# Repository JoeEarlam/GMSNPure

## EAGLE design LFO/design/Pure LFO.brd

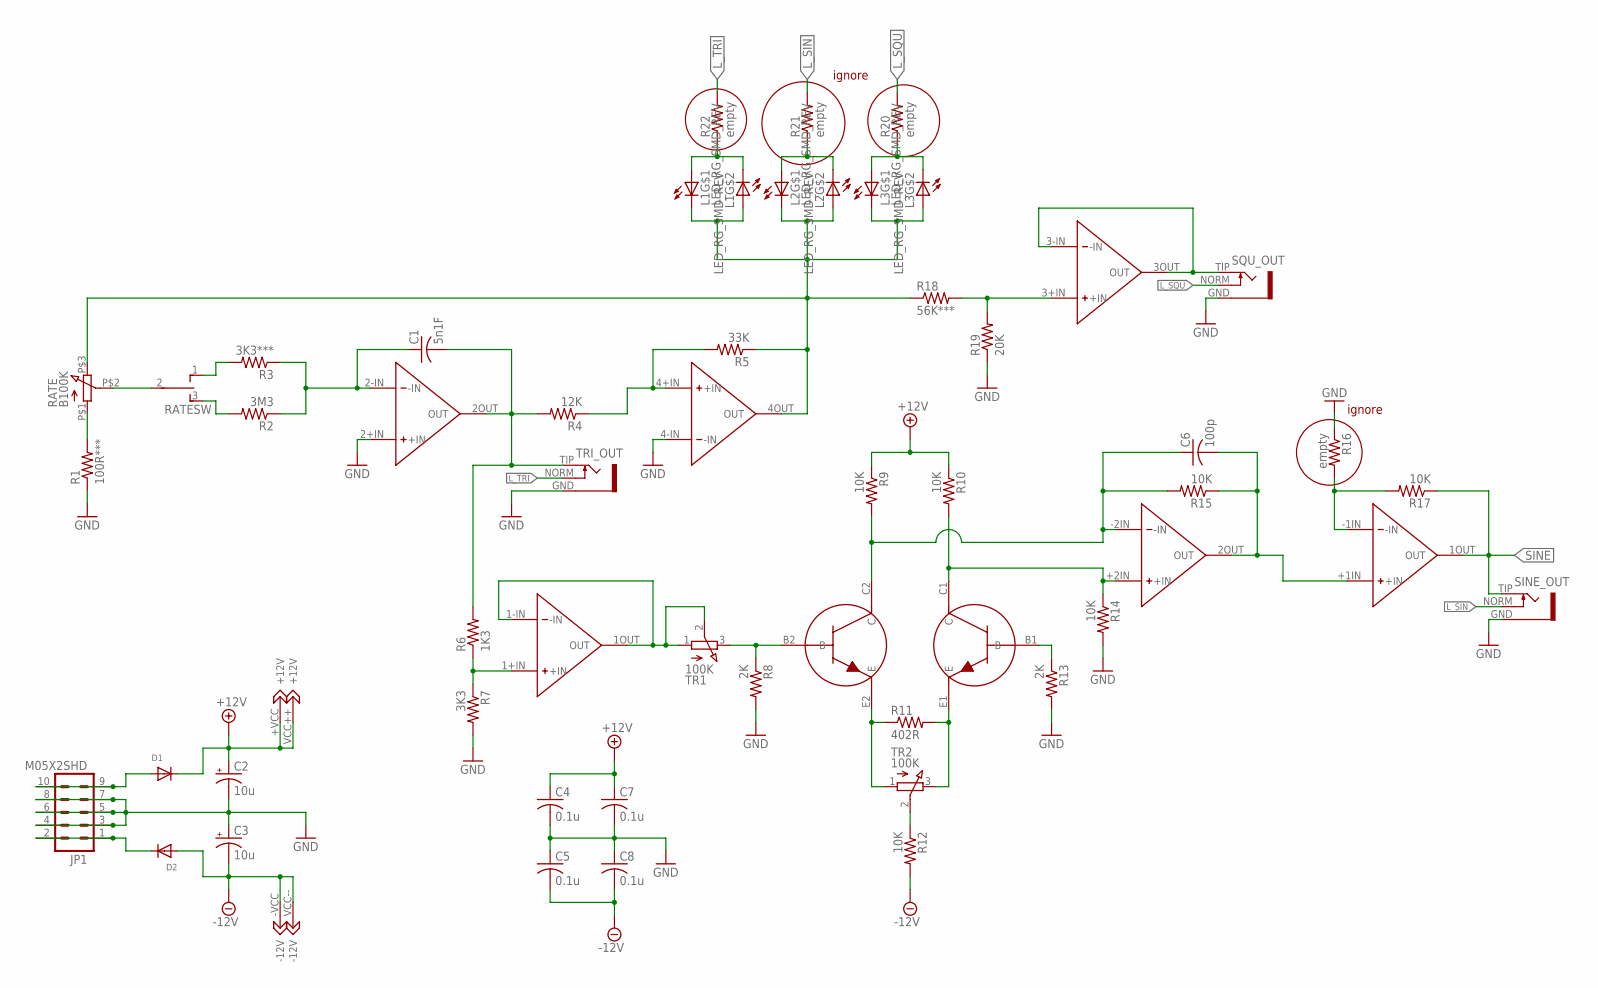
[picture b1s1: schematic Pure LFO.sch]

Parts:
C1: 5n1F; C0805K
C2, C3: 10u; 153CLV-0505
C4, C5, C7, C8: 0.1u; C0805K
C6: 100p; C0805K
D1, D2: DIODESMA; SMADIODE
JP1: M05X2SHD; 2X5-SHROUDED
L1, L2, L3: LED_RG_SMD_REV; LSG_T77K
R1: 100R***; R0805
R2: 3M3; R0805
R3: 3K3***; R0805
R4: 12K; R0805
R5: 33K; R0805
R6: 1K3; R0805
R7: 3K3; R0805
R8, R13: 2K; R0805
R9, R10, R12, R14, R15, R17: 10K; R0805
R11: 402R; R0805
R16, R20, R21, R22: empty; R0805
R18: 56K***; R0805
R19: 20K; R0805
RATE: B100K; Q-POT
RATESW: TOGGLE_ON_OFF_ON
SINE_OUT: S_JACK
SQU_OUT: S_JACK
T3: TRANS_PAIR
TR1, TR2: 100K; TRIM_3269W
TRI_OUT: S_JACK
U1: DUAL_OPAMP
U2: QUAD_OPAMP

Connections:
+12V: C2.+, C4.1, C7.1, D1.C, R9.1, R10.1, U1.+VCC (+12V), U2.VCC++ (+12V)
-12V: C3.-, C5.2, C8.2, D2.A, R12.2, U1.-VCC (-12V), U2.VCC-- (-12V)
GND: C2.-, C3.+, C4.2, C5.1, C7.2, C8.1, JP1.3, JP1.4, JP1.5, JP1.6, JP1.7, JP1.8, R1.1, R7.2, R8.2, R13.2, R14.2, R16.1, R19.1, SINE_OUT.GND, SQU_OUT.GND, TRI_OUT.GND, U2.2+IN (+IN), U2.4-IN (-IN)
L_SIN: R21.2, SINE_OUT.NORM
L_SQU: R20.2, SQU_OUT.NORM
L_TRI: R22.2, TRI_OUT.NORM
unnamed: R1.2, RATE.P$1 (1)
unnamed: RATE.P$2 (2), RATESW.2
unnamed: R3.2, RATESW.1 (O)
unnamed: R2.2, RATESW.3 (S)
unnamed: R18.2, R19.2, U2.3+IN (+IN)
unnamed: C1.1, R2.1, R3.1, U2.2-IN (-IN)
unnamed: C1.2, R4.2, R6.2, TRI_OUT.TIP, U2.2OUT (OUT)
unnamed: SQU_OUT.TIP, U2.3-IN (-IN), U2.3OUT (OUT)
unnamed: R4.1, R5.2, U2.4+IN (+IN)
unnamed: D1.A, JP1.9, JP1.10
unnamed: L1.1 (C), L1.4 (A), L2.1 (C), L2.4 (A), L3.1 (C), L3.4 (A), R5.1, R18.1, RATE.P$3 (3), U2.4OUT (OUT)
unnamed: L1.2 (A), L1.3 (C), R22.1
unnamed: L2.2 (A), L2.3 (C), R21.1
unnamed: L3.2 (A), L3.3 (C), R20.1
unnamed: R11.1, T3.E2 (E), TR2.1
unnamed: R8.1, T3.B2 (B), TR1.3
unnamed: R11.2, T3.E1 (E), TR2.3
unnamed: R12.1, TR2.2
unnamed: R13.1, T3.B1 (B)
unnamed: C6.1, R9.2, R15.2, T3.C2 (C), U1.-2IN (-IN)
unnamed: TR1.1, TR1.2, U2.1-IN (-IN), U2.1OUT (OUT)
unnamed: R10.2, R14.1, T3.C1 (C), U1.+2IN (+IN)
unnamed: R6.1, R7.1, U2.1+IN (+IN)
unnamed: R16.2, R17.2, U1.-1IN (-IN)
unnamed: D2.C, JP1.1, JP1.2
SINE: R17.1, SINE_OUT.TIP, U1.1OUT (OUT)
SINE_PRE: C6.2, R15.1, U1.2OUT (OUT), U1.+1IN (+IN)

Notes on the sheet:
ignore

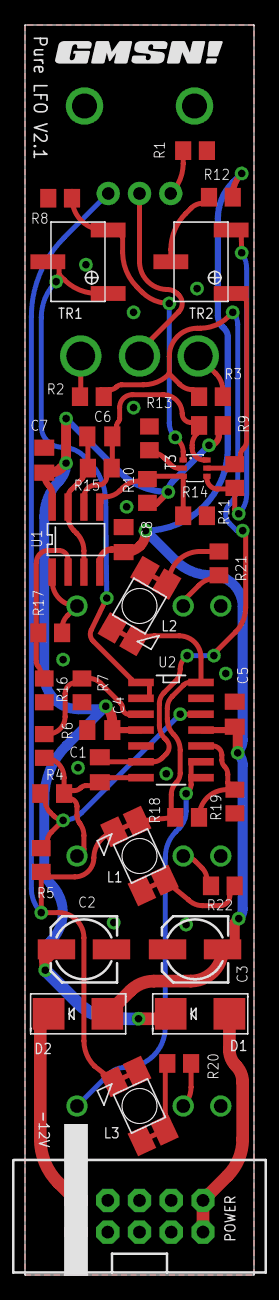
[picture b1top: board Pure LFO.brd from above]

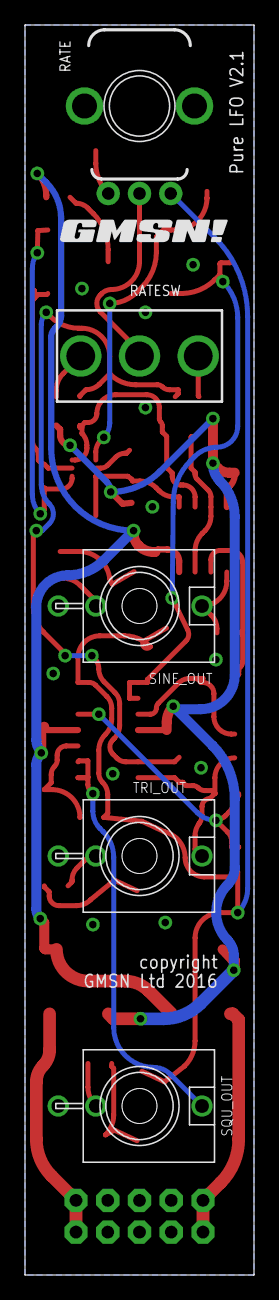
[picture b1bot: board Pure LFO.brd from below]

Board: 2 copper layers, 18.3 x 100.0 mm, 48 parts (6 on the bottom side), 33 nets.

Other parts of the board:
U$1, U$2: GMSN!_LOGO

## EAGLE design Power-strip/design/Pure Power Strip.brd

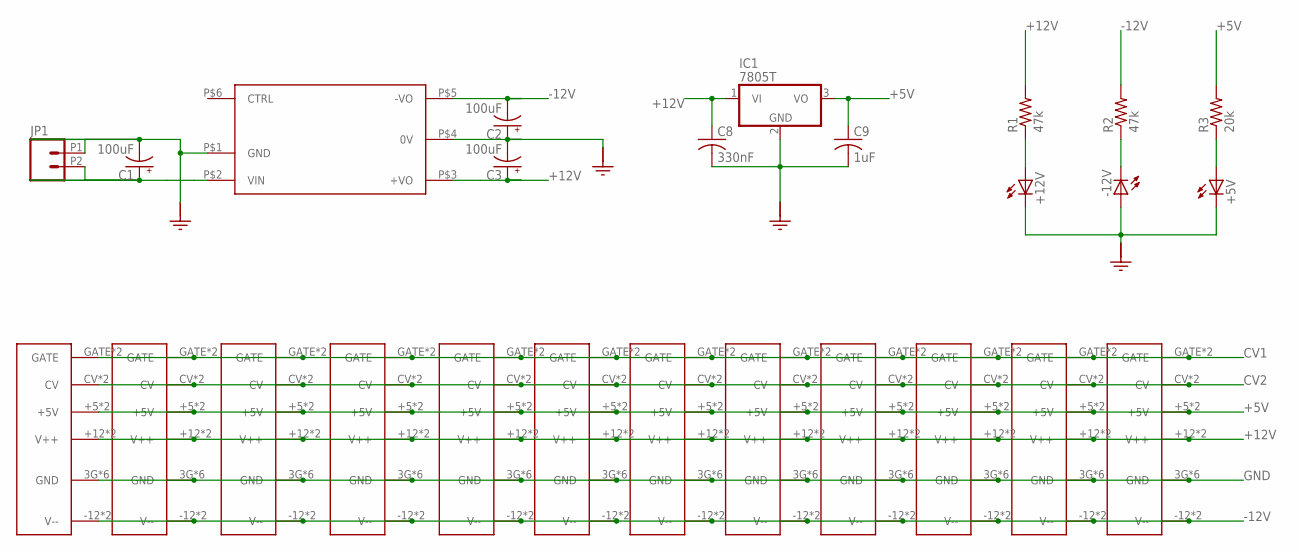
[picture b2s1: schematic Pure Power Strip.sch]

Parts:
+5V, +12V: LED5MM
-12V: LED5MM
C1, C2, C3: 100uF; SANYO-OSCON_D
C8: 330nF; C025-024X044
C9: 1uF; C025-024X044
IC1: 7805T; TO220H
JP1: 1X02_5MM_SCREWTERM
R1, R2: 47k; 0207/10
R3: 20k; 0207/10
U$1: URA241XLD-20WR3
U$2, U$3, U$4, U$5, U$6, U$7, U$8, U$9, U$10, U$11, U$12, U$13: EURO_POWER_16; POWER_SHROUDED

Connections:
+5V: C9.1, IC1.3 (VO), R3.2, U$2.+5 (+5V), U$2.+5A (+5V), U$3.+5 (+5V), U$3.+5A (+5V), U$4.+5 (+5V), U$4.+5A (+5V), U$5.+5 (+5V), U$5.+5A (+5V), U$6.+5 (+5V), U$6.+5A (+5V), U$7.+5 (+5V), U$7.+5A (+5V), U$8.+5 (+5V), U$8.+5A (+5V), U$9.+5 (+5V), U$9.+5A (+5V), U$10.+5 (+5V), U$10.+5A (+5V), U$11.+5 (+5V), U$11.+5A (+5V), U$12.+5 (+5V), U$12.+5A (+5V), U$13.+5 (+5V), U$13.+5A (+5V)
+12V: C3.+, C8.1, IC1.1 (VI), R1.2, U$1.P$3 (+VO), U$2.+12 (V++), U$2.+12A (V++), U$3.+12 (V++), U$3.+12A (V++), U$4.+12 (V++), U$4.+12A (V++), U$5.+12 (V++), U$5.+12A (V++), U$6.+12 (V++), U$6.+12A (V++), U$7.+12 (V++), U$7.+12A (V++), U$8.+12 (V++), U$8.+12A (V++), U$9.+12 (V++), U$9.+12A (V++), U$10.+12 (V++), U$10.+12A (V++), U$11.+12 (V++), U$11.+12A (V++), U$12.+12 (V++), U$12.+12A (V++), U$13.+12 (V++), U$13.+12A (V++)
-12V: C2.-, R2.2, U$1.P$5 (-VO), U$2.-12 (V--), U$2.-12A (V--), U$3.-12 (V--), U$3.-12A (V--), U$4.-12 (V--), U$4.-12A (V--), U$5.-12 (V--), U$5.-12A (V--), U$6.-12 (V--), U$6.-12A (V--), U$7.-12 (V--), U$7.-12A (V--), U$8.-12 (V--), U$8.-12A (V--), U$9.-12 (V--), U$9.-12A (V--), U$10.-12 (V--), U$10.-12A (V--), U$11.-12 (V--), U$11.-12A (V--), U$12.-12 (V--), U$12.-12A (V--), U$13.-12 (V--), U$13.-12A (V--)
CV1: U$2.GATE, U$2.GATEA (GATE), U$3.GATE, U$3.GATEA (GATE), U$4.GATE, U$4.GATEA (GATE), U$5.GATE, U$5.GATEA (GATE), U$6.GATE, U$6.GATEA (GATE), U$7.GATE, U$7.GATEA (GATE), U$8.GATE, U$8.GATEA (GATE), U$9.GATE, U$9.GATEA (GATE), U$10.GATE, U$10.GATEA (GATE), U$11.GATE, U$11.GATEA (GATE), U$12.GATE, U$12.GATEA (GATE), U$13.GATE, U$13.GATEA (GATE)
CV2: U$2.CV, U$2.CVA (CV), U$3.CV, U$3.CVA (CV), U$4.CV, U$4.CVA (CV), U$5.CV, U$5.CVA (CV), U$6.CV, U$6.CVA (CV), U$7.CV, U$7.CVA (CV), U$8.CV, U$8.CVA (CV), U$9.CV, U$9.CVA (CV), U$10.CV, U$10.CVA (CV), U$11.CV, U$11.CVA (CV), U$12.CV, U$12.CVA (CV), U$13.CV, U$13.CVA (CV)
GND: +5V.K (C), +12V.K (C), -12V.A, C1.-, C2.+, C3.-, C8.2, C9.2, IC1.2 (GND), JP1.P1 (2), U$1.P$1 (GND), U$1.P$4 (0V), U$2.3G (GND), U$2.4G (GND), U$2.5G (GND), U$2.6G (GND), U$2.7G (GND), U$2.8G (GND), U$3.3G (GND), U$3.4G (GND), U$3.5G (GND), U$3.6G (GND), U$3.7G (GND), U$3.8G (GND), U$4.3G (GND), U$4.4G (GND), U$4.5G (GND), U$4.6G (GND), U$4.7G (GND), U$4.8G (GND), U$5.3G (GND), U$5.4G (GND), U$5.5G (GND), U$5.6G (GND), U$5.7G (GND), U$5.8G (GND), U$6.3G (GND), U$6.4G (GND), U$6.5G (GND), U$6.6G (GND), U$6.7G (GND), U$6.8G (GND), U$7.3G (GND), U$7.4G (GND), U$7.5G (GND), U$7.6G (GND), U$7.7G (GND), U$7.8G (GND), U$8.3G (GND), U$8.4G (GND), U$8.5G (GND), U$8.6G (GND), U$8.7G (GND), U$8.8G (GND), U$9.3G (GND), U$9.4G (GND), U$9.5G (GND), U$9.6G (GND), U$9.7G (GND), U$9.8G (GND), U$10.3G (GND), U$10.4G (GND), U$10.5G (GND), U$10.6G (GND), U$10.7G (GND), U$10.8G (GND), U$11.3G (GND), U$11.4G (GND), U$11.5G (GND), U$11.6G (GND), U$11.7G (GND), U$11.8G (GND), U$12.3G (GND), U$12.4G (GND), U$12.5G (GND), U$12.6G (GND), U$12.7G (GND), U$12.8G (GND), U$13.3G (GND), U$13.4G (GND), U$13.5G (GND), U$13.6G (GND), U$13.7G (GND), U$13.8G (GND)
unnamed: C1.+, JP1.P2 (1), U$1.P$2 (VIN)
unnamed: +12V.A, R1.1
unnamed: -12V.K (C), R2.1
unnamed: +5V.A, R3.1

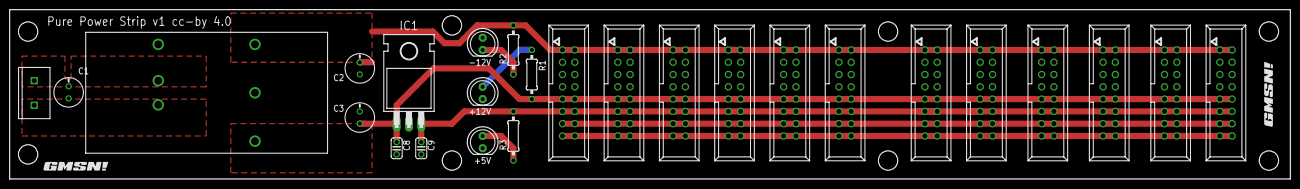
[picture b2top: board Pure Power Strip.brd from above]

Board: 2 copper layers, 264.8 x 35.0 mm, 28 parts (0 on the bottom side), 10 nets.

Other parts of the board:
U$14, U$15: GMSN!_LOGO

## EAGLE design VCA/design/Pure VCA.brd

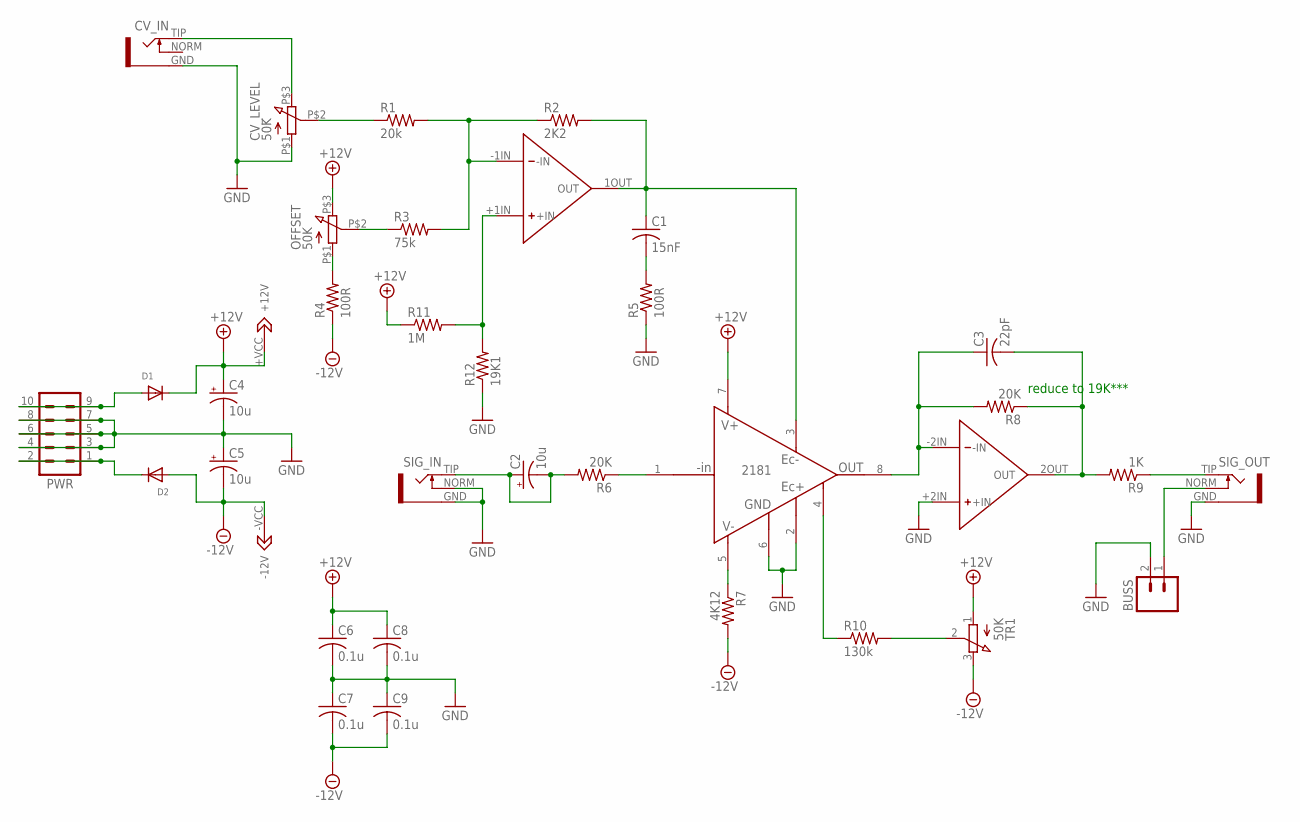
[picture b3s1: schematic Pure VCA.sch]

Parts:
BUSS: M02PTH; 1X02
C1: 15nF; C0805K
C2, C4, C5: 10u; 153CLV-0505
C3: 22pF; C0805K
C6, C7, C8, C9: 0.1u; C0805K
CV_IN: S_JACK
CV_LEVEL: 50K; Q-POT
D1, D2: DIODESMA; SMADIODE
OFFSET: 50K; Q-POT
PWR: M05X2SHD; 2X5-SHROUDED
R1: 20k; R0805
R2: 2K2; R0805
R3: 75k; R0805
R4, R5: 100R; R0805
R6, R8: 20K; R0805
R7: 4K12; R0805
R9: 1K; R0805
R10: 130k; R0805
R11: 1M; R0805
R12: 19K1; R0805
SIG_IN: S_JACK
SIG_OUT: S_JACK
TR1: 50K; TRIM_3269W
U1: DUAL_OPAMP
U2: THAT_2181_SMD; SOIC--8

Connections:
+12V: C4.+, C6.1, C8.1, D1.C, OFFSET.P$3 (3), R11.1, TR1.1, U1.+VCC (+12V), U2.7 (V+)
-12V: C5.-, C7.2, C9.2, D2.A, R4.1, R7.2, TR1.3, U1.-VCC (-12V)
GND: BUSS.2, C4.-, C5.+, C6.2, C7.1, C8.2, C9.1, CV_IN.GND, CV_LEVEL.P$1 (1), PWR.3, PWR.4, PWR.5, PWR.6, PWR.7, PWR.8, R5.1, R12.1, SIG_IN.GND, SIG_IN.NORM, SIG_OUT.GND, U1.+2IN (+IN), U2.2 (EC+), U2.6 (GND)
unnamed: CV_IN.TIP, CV_LEVEL.P$3 (3)
unnamed: R1.2, R2.1, R3.2, U1.-1IN (-IN)
unnamed: CV_LEVEL.P$2 (2), R1.1
unnamed: OFFSET.P$1 (1), R4.2
unnamed: C1.1, R2.2, U1.1OUT (OUT), U2.3 (EC-)
unnamed: OFFSET.P$2 (2), R3.1
unnamed: C1.2, R5.2
unnamed: R9.1, SIG_OUT.TIP
unnamed: R6.1, U2.1 (-IN)
unnamed: C2.+, C2.-, R6.2, SIG_IN.TIP
unnamed: BUSS.1, SIG_OUT.NORM
unnamed: R7.1, U2.5 (V-)
unnamed: R11.2, R12.2, U1.+1IN (+IN)
unnamed: C3.1, R8.2, U1.-2IN (-IN), U2.8 (OUT)
unnamed: C3.2, R8.1, R9.2, U1.2OUT (OUT)
unnamed: R10.1, U2.4 (SYM)
unnamed: R10.2, TR1.2
unnamed: D1.A, PWR.9, PWR.10
unnamed: D2.C, PWR.1, PWR.2

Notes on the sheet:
reduce to 19K***

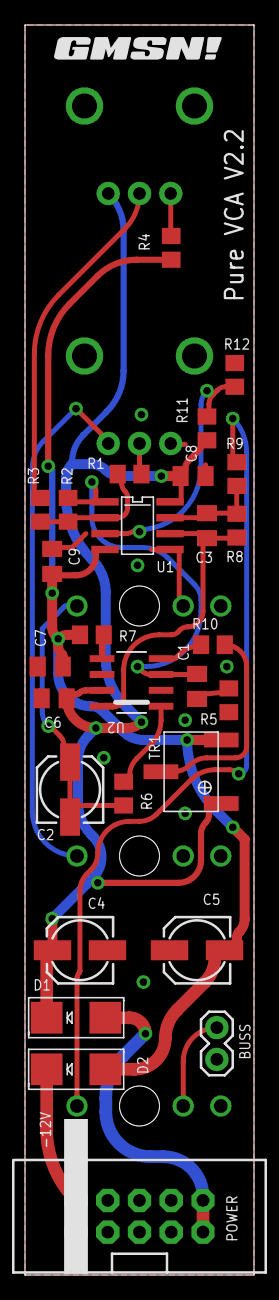
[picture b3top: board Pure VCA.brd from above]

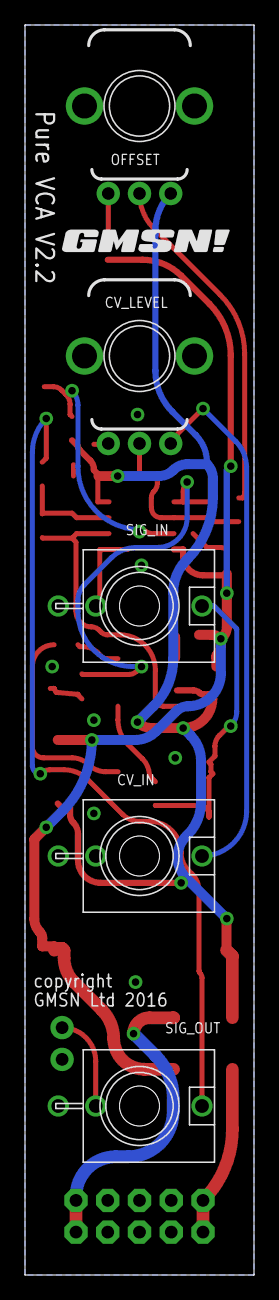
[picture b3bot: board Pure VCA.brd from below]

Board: 2 copper layers, 18.3 x 100.0 mm, 35 parts (6 on the bottom side), 22 nets.

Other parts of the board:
U$1, U$2: GMSN!_LOGO

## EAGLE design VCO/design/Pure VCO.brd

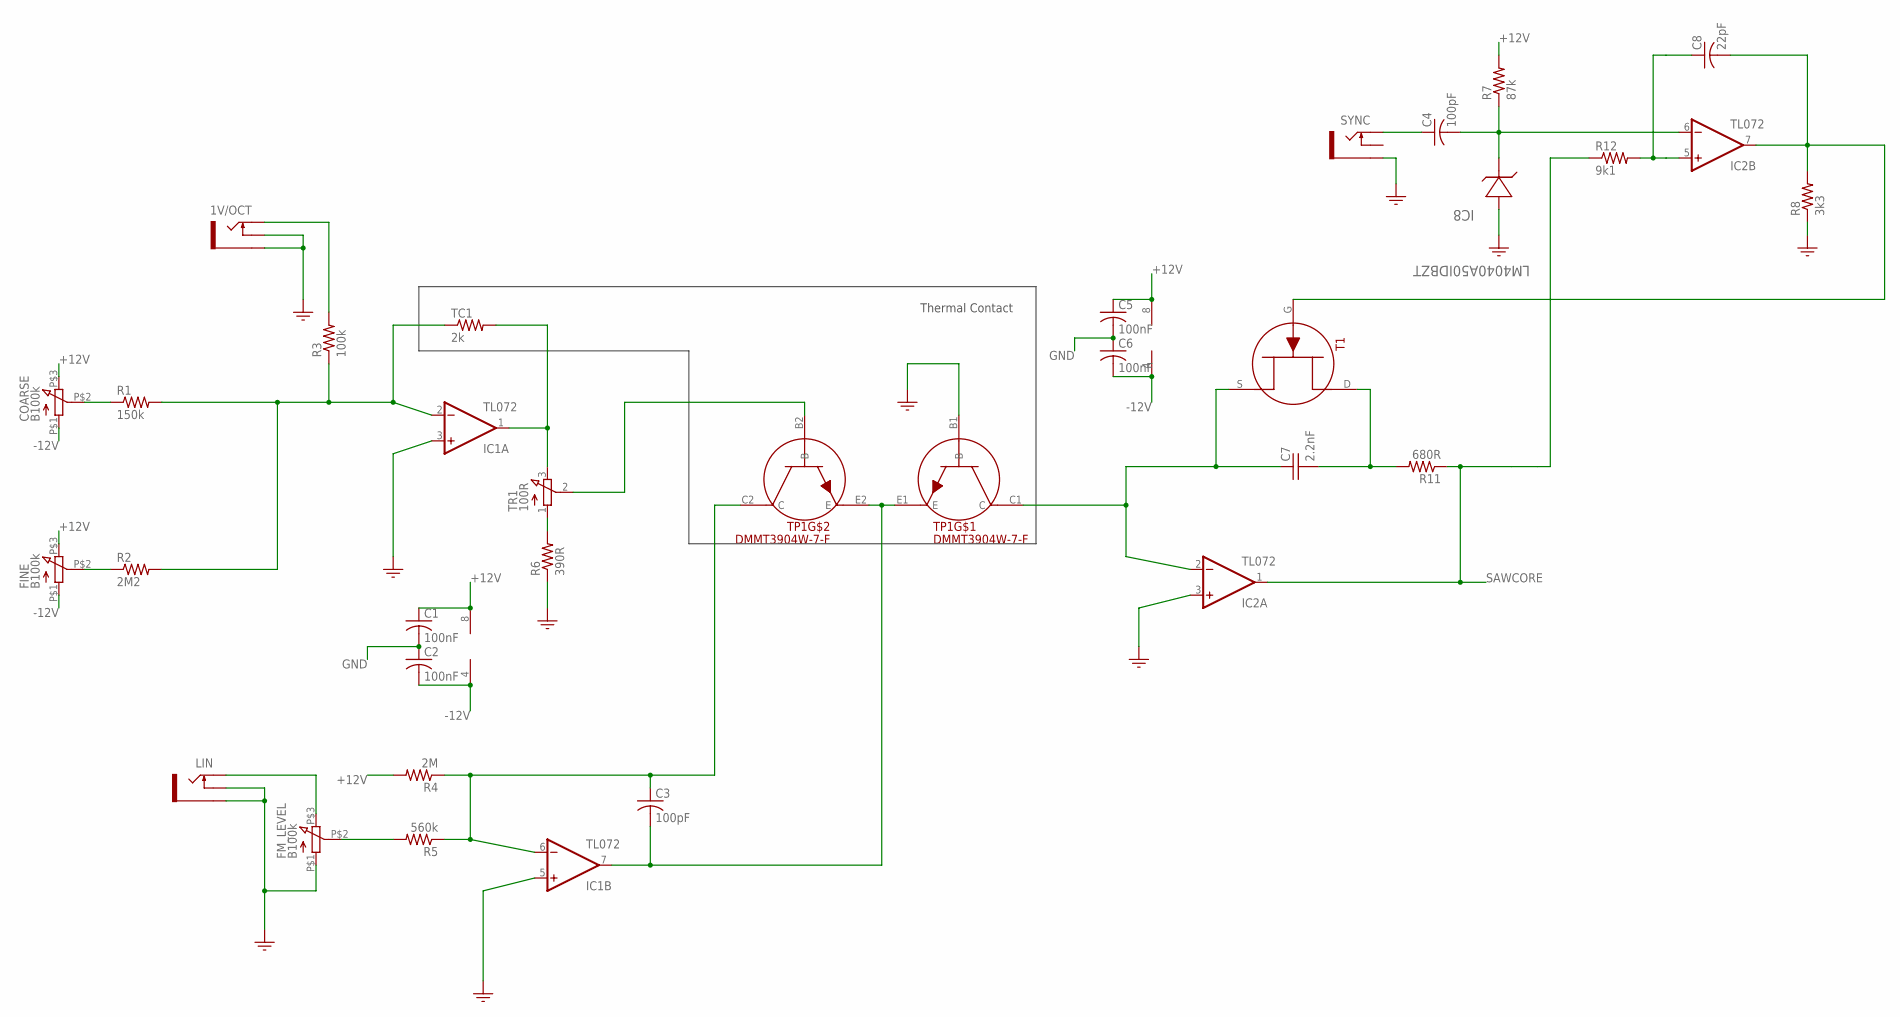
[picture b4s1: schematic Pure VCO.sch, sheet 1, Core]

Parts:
1V/OCT: PJ301M-12
C1, C2, C5, C6: 100nF; C0805
C3, C4: 100pF; C0805
C7: 2.2nF; POLY_CAP
C8: 22pF; C0805
COARSE: B100k; POTENTIOMETER_9MM
FINE: B100k; POTENTIOMETER_9MM
FM_LEVEL: B100k; POTENTIOMETER_9MM
IC1, IC2: TL072; SO08
IC8: LM4040A50IDBZT; SOT95P237X112-3N
LIN: PJ301M-12
R1: 150k; R0805
R2: 2M2; R0805
R3: 100k; R0805
R4: 2M; R0805
R5: 560k; R0805
R6: 390R; R0805
R7: 87k; R0805
R8: 3k3; R0805
R11: 680R; R0805
R12: 9k1; R0805
SYNC: PJ301M-12
T1: MMBFJ309; N_CHN
TC1: 2k; 0204/7
TP1: DMMT3904W-7-F; TRANS_PAIR
TR1: 100R; TRIMMER_TH

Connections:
+12V: C1.1, C5.1, COARSE.P$3 (3), FINE.P$3 (3), IC1.8 (V+), IC2.8 (V+), R4.2, R7.2; also elsewhere on the board
-12V: C2.2, C6.2, COARSE.P$1 (1), FINE.P$1 (1), IC1.4 (V-), IC2.4 (V-); also elsewhere on the board
GND: 1V/OCT.GND (SLEEVE), 1V/OCT.NORM (SWITCH), C1.2, C2.1, C5.2, C6.1, FM_LEVEL.P$1 (1), IC1.3 (+IN), IC1.5 (+IN), IC2.3 (+IN), IC8.2 (ANODE), LIN.GND (SLEEVE), LIN.NORM (SWITCH), R6.1, R8.1, SYNC.GND (SLEEVE), TP1.B1 (B); also elsewhere on the board
unnamed: COARSE.P$2 (2), R1.1
unnamed: IC1.2 (-IN), R1.2, R2.2, R3.1, TC1.1
unnamed: FINE.P$2 (2), R2.1
unnamed: IC1.1 (OUT), TC1.2, TR1.3
unnamed: R6.2, TR1.1
unnamed: 1V/OCT.TIP, R3.2
unnamed: TP1.B2 (B), TR1.2
unnamed: C7.2 (-), R11.2, T1.D
unnamed: C3.1, IC1.6 (-IN), R4.1, R5.1, TP1.C2 (C)
unnamed: C7.1 (+), IC2.2 (-IN), T1.S, TP1.C1 (C)
unnamed: FM_LEVEL.P$3 (3), LIN.TIP
unnamed: C8.1, IC2.5 (+IN), R12.2
unnamed: FM_LEVEL.P$2 (2), R5.2
unnamed: C3.2, IC1.7 (OUT), TP1.E1 (E), TP1.E2 (E)
unnamed: C8.2, IC2.7 (OUT), R8.2, T1.G
unnamed: C4.1, SYNC.TIP
unnamed: C4.2, IC2.6 (-IN), IC8.1 (CATHODE), R7.1
SAWCORE: IC2.1 (OUT), R11.1, R12.1; also elsewhere on the board

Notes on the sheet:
Thermal Contact

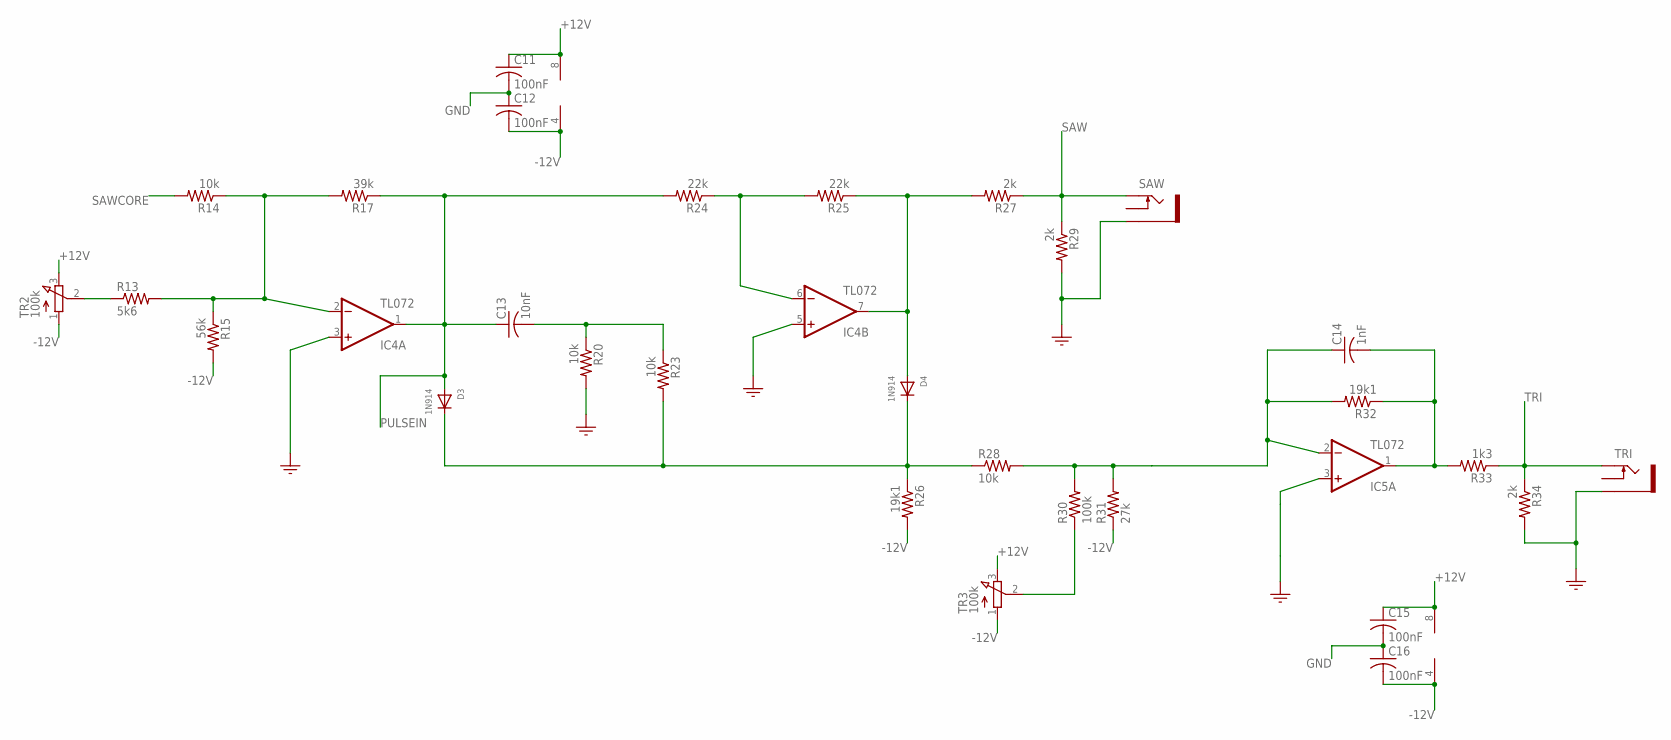
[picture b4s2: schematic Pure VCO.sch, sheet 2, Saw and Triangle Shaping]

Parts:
C11, C12, C15, C16: 100nF; C0805
C13: 10nF; C0805
C14: 1nF; C0805
D3, D4: 1N914; SOD-323F
IC4, IC5: TL072; SO08
R13: 5k6; R0805
R14, R20, R23, R28: 10k; R0805
R15: 56k; R0805
R17: 39k; R0805
R24, R25: 22k; R0805
R26, R32: 19k1; R0805
R27, R29, R34: 2k; R0805
R30: 100k; R0805
R31: 27k; R0805
R33: 1k3; R0805
SAW: PJ301M-12
TR2, TR3: 100k; TRIMMER_TH
TRI: PJ301M-12

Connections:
+12V: C11.1, C15.1, IC4.8 (V+), IC5.8 (V+), TR2.3, TR3.3; also elsewhere on the board
-12V: C12.2, C16.2, IC4.4 (V-), IC5.4 (V-), R15.2, R26.2, R31.1, TR2.1, TR3.1; also elsewhere on the board
GND: C11.2, C12.1, C15.2, C16.1, IC4.3 (+IN), IC4.5 (+IN), IC5.3 (+IN), R20.2, R29.2, R34.2, SAW.GND (SLEEVE), TRI.GND (SLEEVE); also elsewhere on the board
unnamed: R13.1, TR2.2
unnamed: IC4.2 (-IN), R13.2, R14.1, R15.1, R17.2
unnamed: C13.2, R20.1, R23.1
unnamed: R30.1, TR3.2
unnamed: IC4.6 (-IN), R24.1, R25.2
unnamed: D4.A, IC4.7 (OUT), R25.1, R27.2
unnamed: D3.C, D4.C, R23.2, R26.1, R28.1
unnamed: C14.1, IC5.2 (-IN), R28.2, R30.2, R31.2, R32.2
unnamed: C14.2, IC5.1 (OUT), R32.1, R33.2
PULSEIN: C13.1, D3.A, IC4.1 (OUT), R17.1, R24.2; also elsewhere on the board
SAW: R27.1, R29.1, SAW.TIP; also elsewhere on the board
SAWCORE: R14.2; also elsewhere on the board
TRI: R33.1, R34.1, TRI.TIP; also elsewhere on the board

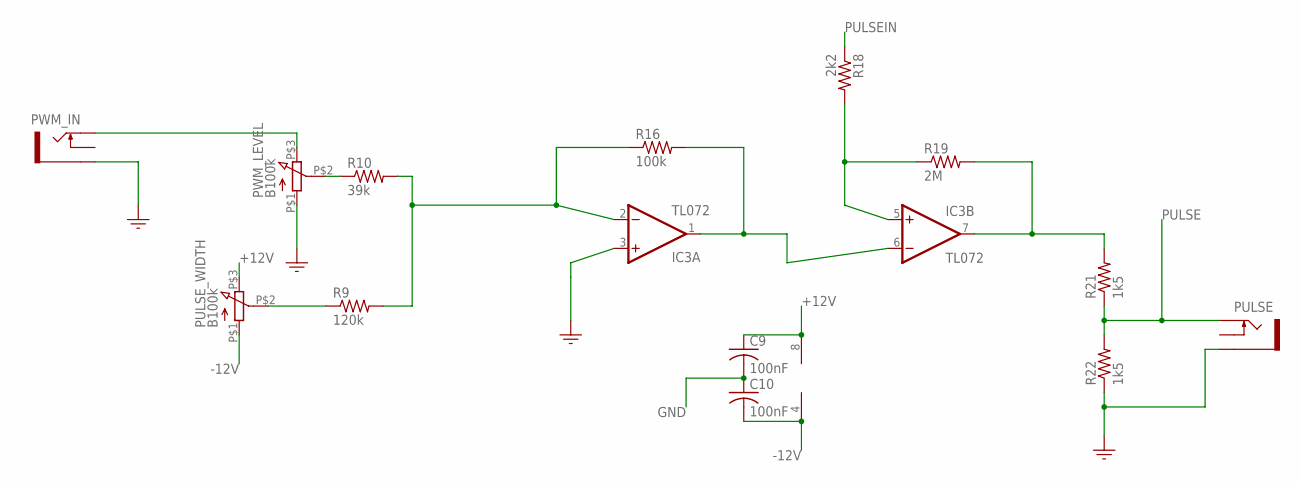
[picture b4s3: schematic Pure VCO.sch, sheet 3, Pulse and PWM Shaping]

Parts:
C9, C10: 100nF; C0805
IC3: TL072; SO08
PULSE: PJ301M-12
PULSE_WIDTH: B100k; POTENTIOMETER_9MM
PWM_IN: PJ301M-12
PWM_LEVEL: B100k; POTENTIOMETER_9MM
R9: 120k; R0805
R10: 39k; R0805
R16: 100k; R0805
R18: 2k2; R0805
R19: 2M; R0805
R21, R22: 1k5; R0805

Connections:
+12V: C9.1, IC3.8 (V+), PULSE_WIDTH.P$3 (3); also elsewhere on the board
-12V: C10.2, IC3.4 (V-), PULSE_WIDTH.P$1 (1); also elsewhere on the board
GND: C9.2, C10.1, IC3.3 (+IN), PULSE.GND (SLEEVE), PWM_IN.GND (SLEEVE), PWM_LEVEL.P$1 (1), R22.1; also elsewhere on the board
unnamed: IC3.1 (OUT), IC3.6 (-IN), R16.2
unnamed: IC3.5 (+IN), R18.2, R19.1
unnamed: IC3.7 (OUT), R19.2, R21.2
unnamed: PULSE_WIDTH.P$2 (2), R9.1
unnamed: PWM_IN.TIP, PWM_LEVEL.P$3 (3)
unnamed: IC3.2 (-IN), R9.2, R10.2, R16.1
unnamed: PWM_LEVEL.P$2 (2), R10.1
PULSE: PULSE.TIP, R21.1, R22.2; also elsewhere on the board
PULSEIN: R18.1; also elsewhere on the board

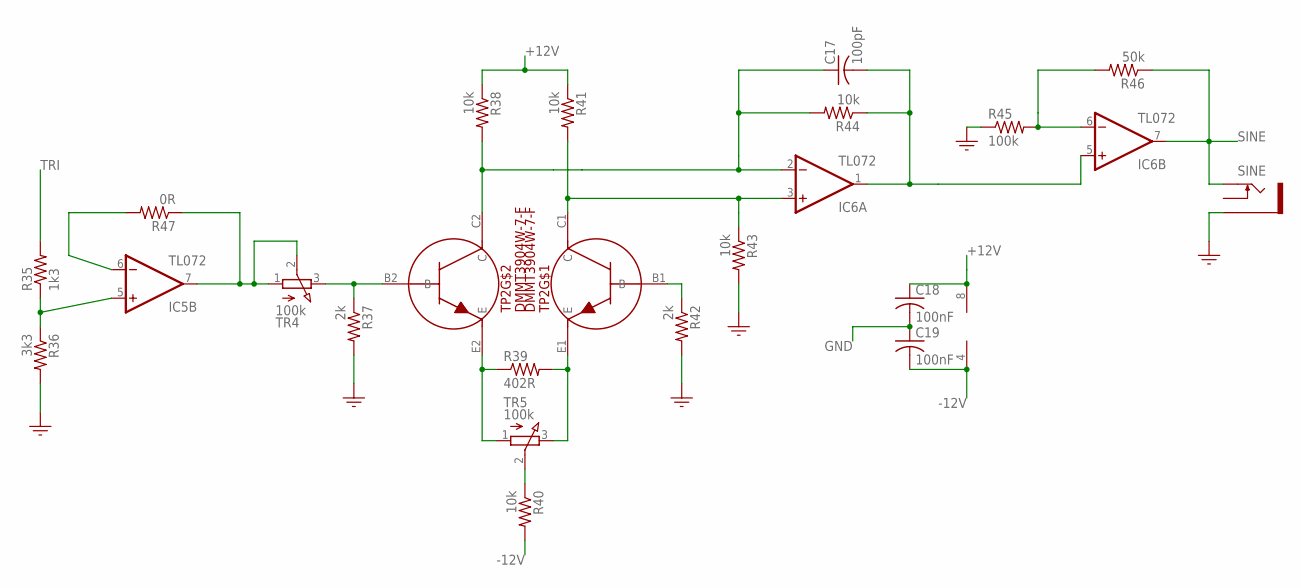
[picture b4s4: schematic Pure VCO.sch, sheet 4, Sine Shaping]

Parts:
C17: 100pF; C0805
C18, C19: 100nF; C0805
IC5, IC6: TL072; SO08
R35: 1k3; R0805
R36: 3k3; R0805
R37, R42: 2k; R0805
R38, R40, R41, R43, R44: 10k; R0805
R39: 402R; R0805
R45: 100k; R0805
R46: 50k; R0805
R47: 0R; R0805
SINE: PJ301M-12
TP2: DMMT3904W-7-F; TRANS_PAIR
TR4, TR5: 100k; TRIMMER_TH

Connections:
+12V: C18.1, IC6.8 (V+), R38.1, R41.1; also elsewhere on the board
-12V: C19.2, IC6.4 (V-), R40.2; also elsewhere on the board
GND: C18.2, C19.1, R36.2, R37.2, R42.2, R43.2, R45.1, SINE.GND (SLEEVE); also elsewhere on the board
unnamed: C17.1, IC6.2 (-IN), R38.2, R44.2, TP2.C2 (C)
unnamed: IC5.6 (-IN), R47.2
unnamed: IC5.7 (OUT), R47.1, TR4.1, TR4.2
unnamed: R37.1, TP2.B2 (B), TR4.3
unnamed: R39.1, TP2.E2 (E), TR5.1
unnamed: R39.2, TP2.E1 (E), TR5.3
unnamed: R40.1, TR5.2
unnamed: R42.1, TP2.B1 (B)
unnamed: IC6.3 (+IN), R41.2, R43.1, TP2.C1 (C)
unnamed: IC5.5 (+IN), R35.1, R36.1
unnamed: IC6.6 (-IN), R45.2, R46.2
SINE: IC6.7 (OUT), R46.1, SINE.TIP; also elsewhere on the board
SINE_PRE1: C17.2, IC6.1 (OUT), IC6.5 (+IN), R44.1
TRI: R35.2; also elsewhere on the board

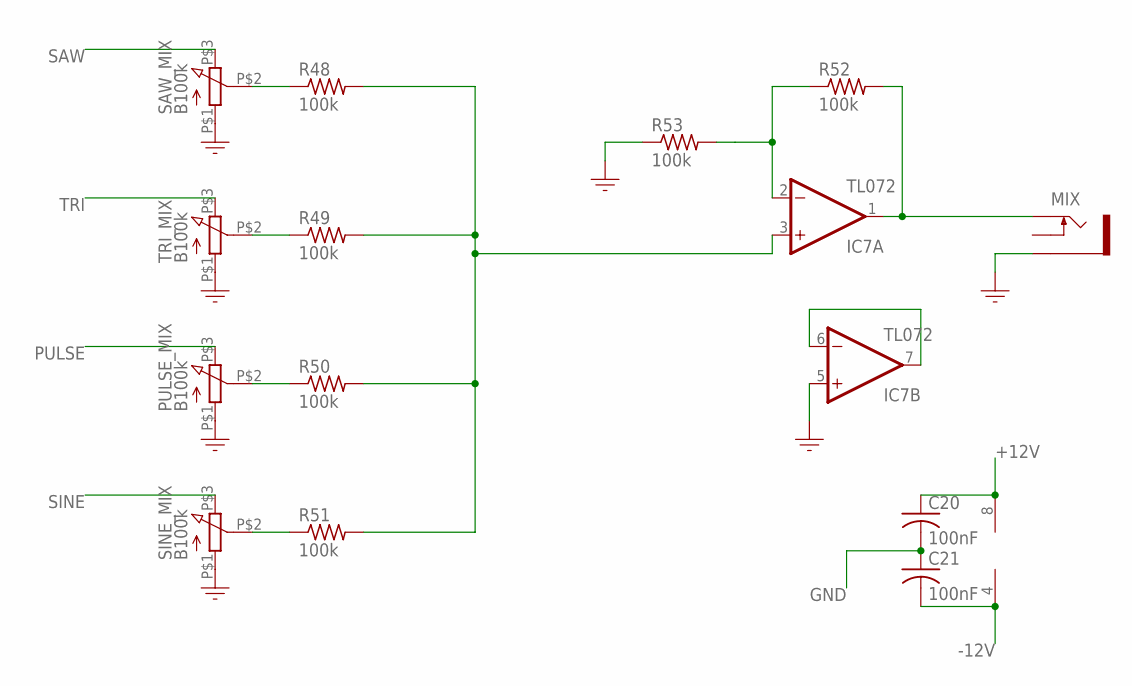
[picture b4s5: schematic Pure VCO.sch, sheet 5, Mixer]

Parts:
C20, C21: 100nF; C0805
IC7: TL072; SO08
MIX: PJ301M-12
PULSE_MIX: B100k; POTENTIOMETER_9MM
R48, R49, R50, R51, R52, R53: 100k; R0805
SAW_MIX: B100k; POTENTIOMETER_9MM
SINE_MIX: B100k; POTENTIOMETER_9MM
TRI_MIX: B100k; POTENTIOMETER_9MM

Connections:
+12V: C20.1, IC7.8 (V+); also elsewhere on the board
-12V: C21.2, IC7.4 (V-); also elsewhere on the board
GND: C20.2, C21.1, IC7.5 (+IN), MIX.GND (SLEEVE), PULSE_MIX.P$1 (1), R53.1, SAW_MIX.P$1 (1), SINE_MIX.P$1 (1), TRI_MIX.P$1 (1); also elsewhere on the board
unnamed: IC7.6 (-IN), IC7.7 (OUT)
unnamed: IC7.3 (+IN), R48.2, R49.2, R50.2, R51.2
unnamed: R48.1, SAW_MIX.P$2 (2)
unnamed: R49.1, TRI_MIX.P$2 (2)
unnamed: PULSE_MIX.P$2 (2), R50.1
unnamed: R51.1, SINE_MIX.P$2 (2)
unnamed: IC7.2 (-IN), R52.1, R53.2
unnamed: IC7.1 (OUT), MIX.TIP, R52.2
PULSE: PULSE_MIX.P$3 (3); also elsewhere on the board
SAW: SAW_MIX.P$3 (3); also elsewhere on the board
SINE: SINE_MIX.P$3 (3); also elsewhere on the board
TRI: TRI_MIX.P$3 (3); also elsewhere on the board

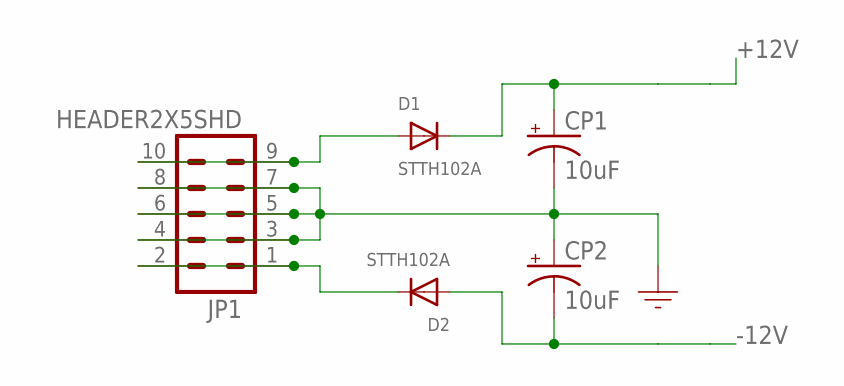
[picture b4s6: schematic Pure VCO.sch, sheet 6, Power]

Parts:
CP1, CP2: 10uF; 153CLV-0505
D1, D2: STTH102A; SMADIODE
JP1: HEADER2X5SHD; 2X5-SHROUDED

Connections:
+12V: CP1.+, D1.C; also elsewhere on the board
-12V: CP2.-, D2.A; also elsewhere on the board
GND: CP1.-, CP2.+, JP1.3, JP1.4, JP1.5, JP1.6, JP1.7, JP1.8; also elsewhere on the board
unnamed: D1.A, JP1.9, JP1.10
unnamed: D2.C, JP1.1, JP1.2

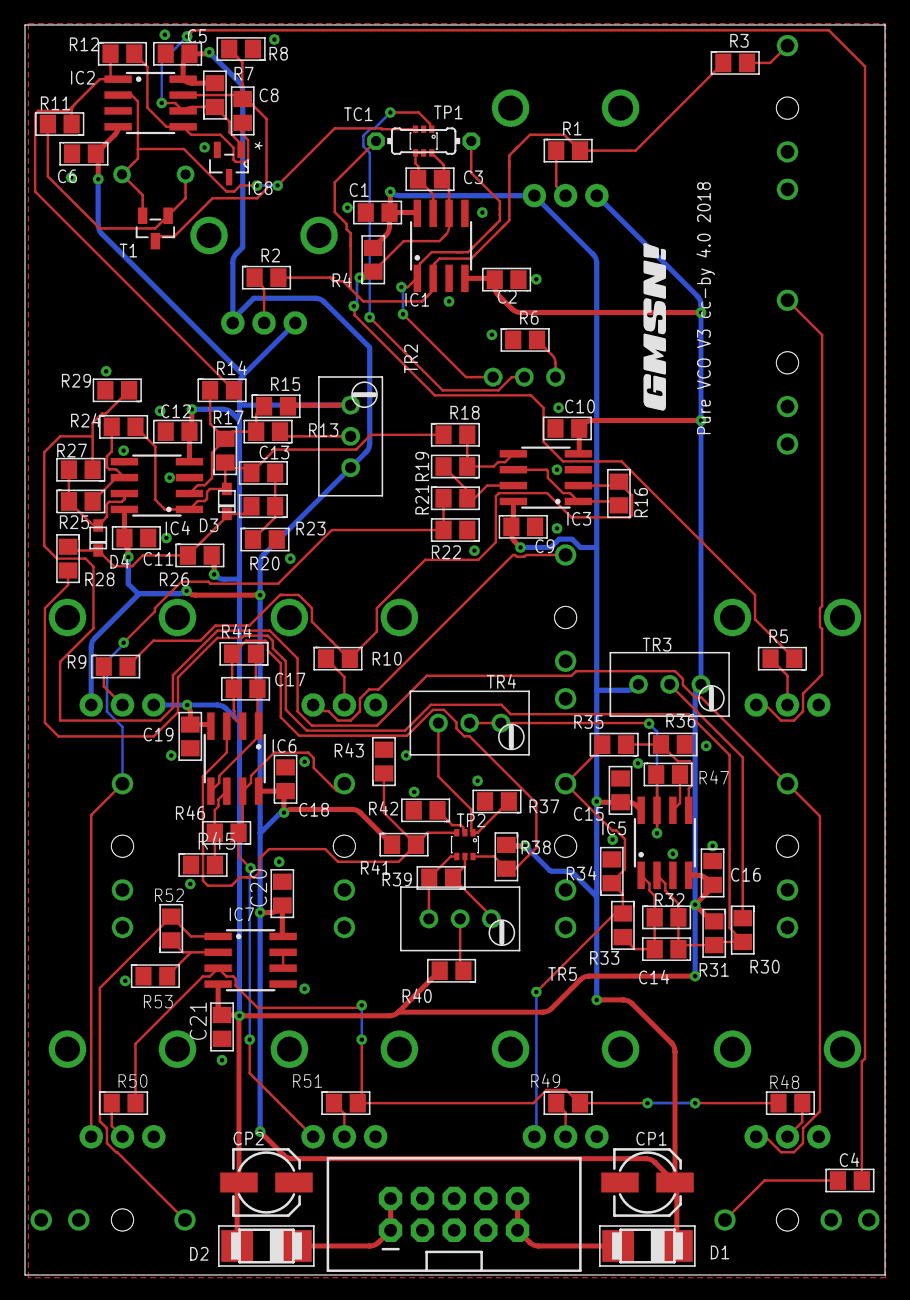
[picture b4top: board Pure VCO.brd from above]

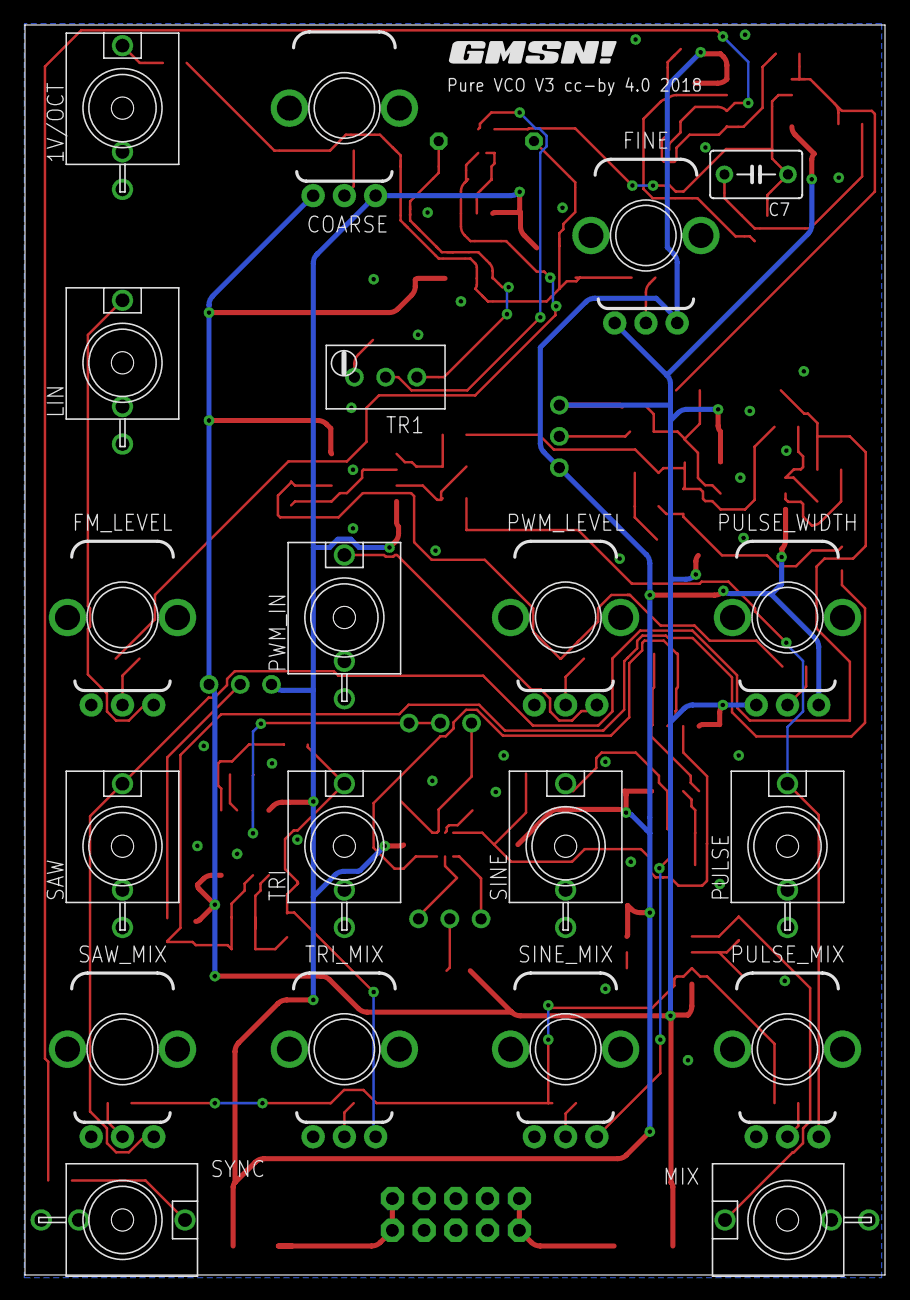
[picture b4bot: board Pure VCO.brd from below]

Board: 2 copper layers, 68.8 x 100.0 mm, 118 parts (21 on the bottom side), 64 nets.

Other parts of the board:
U$1, U$2: GMSN!_LOGO

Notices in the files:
Power-strip/design/Pure Power Strip.brd:
Pure Power Strip v1 cc-by 4.0
VCO/design/Pure VCO.brd:
Pure VCO V3 cc-by 4.0 2018
parts and their libraries:
SparkFun-Connectors: Licensing: CC v3.0 Share-Alike You are welcome to use this library for commercial purposes.
